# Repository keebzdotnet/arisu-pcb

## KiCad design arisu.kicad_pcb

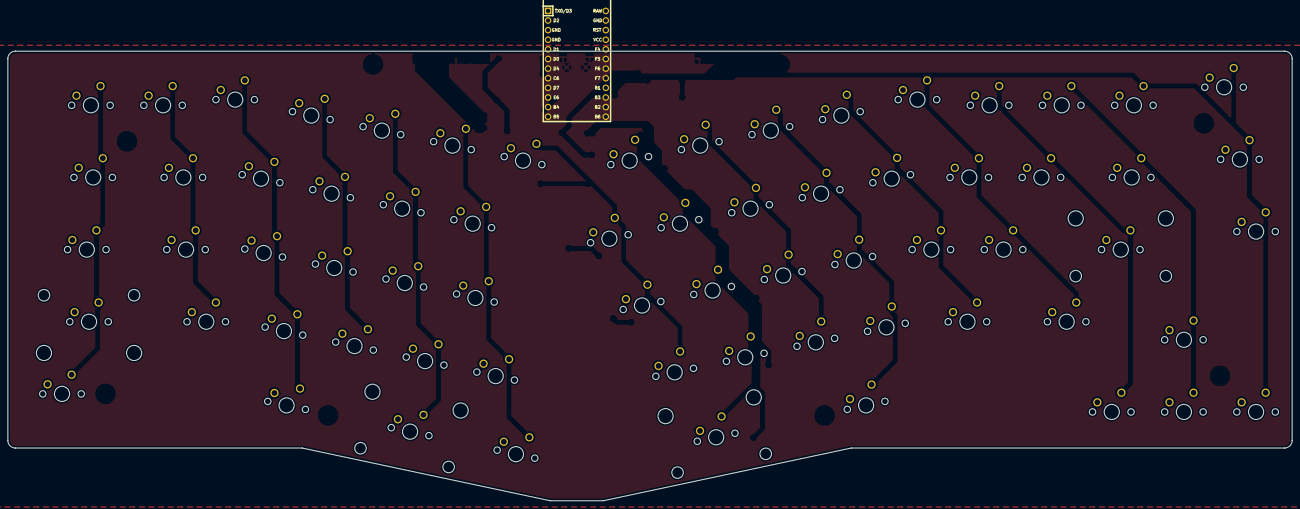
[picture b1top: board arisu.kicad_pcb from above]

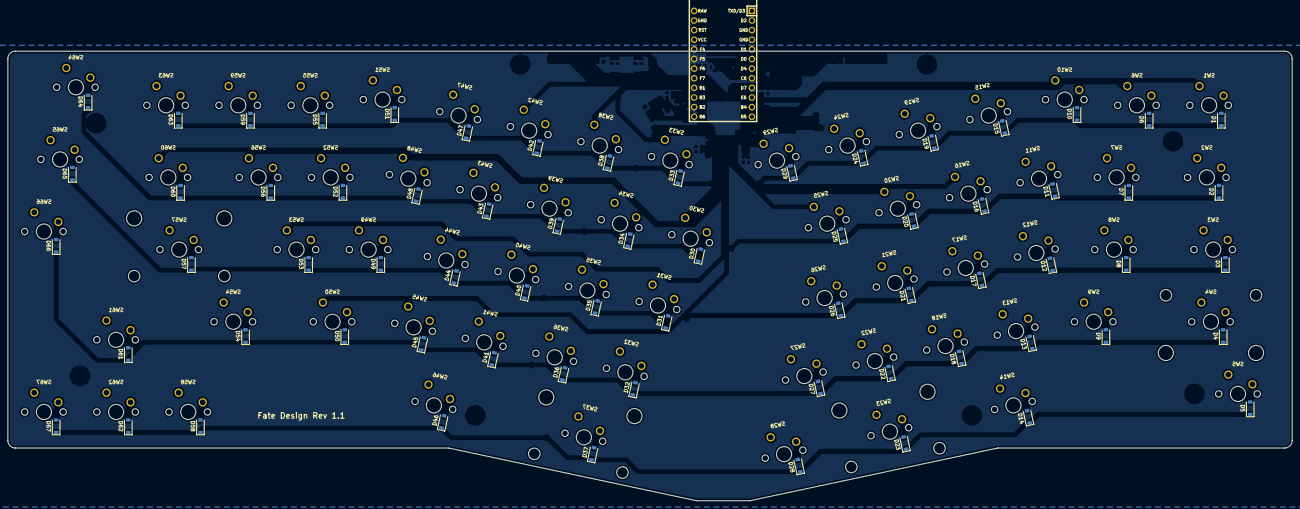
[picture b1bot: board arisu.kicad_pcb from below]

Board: 2 copper layers, 339.1 x 118.7 mm, 135 parts (67 on the bottom side), 82 nets, no tracks yet.

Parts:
D1, D2, D3, D4, D5, D6, D7, D8, D9, D10, D11, D12, D13, D14, D15, D16, D17, D18, D19, D20, D21, D22, D23, D24, D25, D26, D27, D28, D29, D30, D31, D32, D33, D34, D35, D36, D37, D38, D39, D40, D41, D42, D43, D44, D45, D46, D47, D48, D49, D50, D51, D52, D53, D54, D55, D56, D57, D58, D59, D60, D61, D62, D63, D64, D65, D66, D67: D; D_SOD-123
SW1, SW6, SW7, SW8, SW9, SW10, SW11, SW12, SW13, SW15, SW16, SW17, SW18, SW19, SW20, SW21, SW22, SW24, SW25, SW26, SW27, SW28, SW29, SW30, SW31, SW32, SW33, SW34, SW35, SW36, SW38, SW39, SW40, SW41, SW42, SW43, SW44, SW45, SW47, SW48, SW49, SW50, SW51, SW52, SW53, SW55, SW56, SW58, SW59, SW61, SW62, SW63, SW64, SW65, SW66, SW67: SW_Push; SW_Cherry_MX_1.00u_PCB
SW2, SW5, SW14, SW46, SW60: SW_Push; SW_Cherry_MX_1.50u_PCB
SW3, SW54: SW_Push; SW_Cherry_MX_1.75u_PCB
SW4: SW_Push; SW_Cherry_MX_2.25u_PCB
SW23: SW_Push; SW_Cherry_MX_2.00u_PCB_ReversedStabilizers
SW37: SW_Push; SW_Cherry_MX_2.75u_PCB_ReversedStabilizers
SW57: SW_Push; SW_Cherry_MX_2.25u_PCB_ReversedStabilizers
U1: ProMicro; ArduinoProMicro

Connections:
/matrix/col0: SW1.1, SW2.1, SW3.1, SW4.1, SW5.1, SW6.1, SW7.1, SW8.1, SW9.1, U1.12
/matrix/col2: SW10.1, SW11.1, SW12.1, SW13.1, SW14.1
/matrix/col3: SW15.1, SW16.1, SW17.1, SW18.1, U1.11
/matrix/col4: SW19.1, SW20.1, SW21.1, SW22.1, SW23.1, SW24.1, SW25.1, SW26.1, SW27.1, SW28.1, U1.10
/matrix/col6: SW29.1, SW30.1, SW31.1, SW32.1, SW33.1, SW34.1, SW35.1, SW36.1, SW37.1, U1.9
/matrix/col8: SW38.1, SW39.1, SW40.1, SW41.1, U1.8
/matrix/col9: SW42.1, SW43.1, SW44.1, SW45.1, SW46.1
/matrix/col10: SW47.1, SW48.1, SW49.1, SW50.1, SW51.1, SW52.1, SW53.1, SW54.1, U1.7
/matrix/col12: SW55.1, SW56.1, SW57.1, SW58.1, U1.6
/matrix/col13: SW59.1, SW60.1, SW61.1, SW62.1
/matrix/col14: SW63.1, SW64.1, SW65.1, SW66.1, SW67.1, U1.5
/matrix/row0: D1.1, D6.1, D10.1, D15.1, D19.1, D24.1, D29.1, D33.1, D38.1, D42.1, D47.1, D51.1, D55.1, D59.1, D63.1, U1.20
/matrix/row1: D2.1, D3.1, D7.1, D8.1, D11.1, D12.1, D16.1, D17.1, D20.1, D21.1, D25.1, D26.1, D30.1, D31.1, D34.1, D35.1, D39.1, D40.1, D43.1, D44.1, D48.1, D49.1, D52.1, D53.1, D56.1, D57.1, D60.1, D64.1, D65.1, U1.18, U1.19
/matrix/row3: D4.1, D9.1, D13.1, D18.1, D22.1, D27.1, D32.1, D36.1, D41.1, D45.1, D50.1, D54.1, D61.1, D66.1
/matrix/row4: D5.1, D14.1, D23.1, D28.1, D37.1, D46.1, D58.1, D62.1, D67.1, U1.16
unnamed: D1.2, SW1.2
unnamed: D2.2, SW2.2
unnamed: D3.2, SW3.2
unnamed: D4.2, SW4.2
unnamed: D5.2, SW5.2
unnamed: D6.2, SW6.2
unnamed: D7.2, SW7.2
unnamed: D8.2, SW8.2
unnamed: D9.2, SW9.2
unnamed: D10.2, SW10.2
unnamed: D11.2, SW11.2
unnamed: D12.2, SW12.2
unnamed: D13.2, SW13.2
unnamed: D14.2, SW14.2
unnamed: D15.2, SW15.2
unnamed: D16.2, SW16.2
unnamed: D17.2, SW17.2
unnamed: D18.2, SW18.2
unnamed: D19.2, SW19.2
unnamed: D20.2, SW20.2
unnamed: D21.2, SW21.2
unnamed: D22.2, SW22.2
unnamed: D23.2, SW23.2
unnamed: D24.2, SW24.2
unnamed: D25.2, SW25.2
unnamed: D26.2, SW26.2
unnamed: D27.2, SW27.2
unnamed: D28.2, SW28.2
unnamed: D29.2, SW29.2
unnamed: D30.2, SW30.2
unnamed: D31.2, SW31.2
unnamed: D32.2, SW32.2
unnamed: D33.2, SW33.2
unnamed: D34.2, SW34.2
unnamed: D35.2, SW35.2
unnamed: D36.2, SW36.2
unnamed: D37.2, SW37.2
unnamed: D38.2, SW38.2
unnamed: D39.2, SW39.2
unnamed: D40.2, SW40.2
unnamed: D41.2, SW41.2
unnamed: D42.2, SW42.2
unnamed: D43.2, SW43.2
unnamed: D44.2, SW44.2
unnamed: D45.2, SW45.2
unnamed: D46.2, SW46.2
unnamed: D47.2, SW47.2
unnamed: D48.2, SW48.2
unnamed: D49.2, SW49.2
unnamed: D50.2, SW50.2
unnamed: D51.2, SW51.2
unnamed: D52.2, SW52.2
unnamed: D53.2, SW53.2
unnamed: D54.2, SW54.2
unnamed: D55.2, SW55.2
unnamed: D56.2, SW56.2
unnamed: D57.2, SW57.2
unnamed: D58.2, SW58.2
unnamed: D59.2, SW59.2
unnamed: D60.2, SW60.2
unnamed: D61.2, SW61.2
unnamed: D62.2, SW62.2
unnamed: D63.2, SW63.2
unnamed: D64.2, SW64.2
unnamed: D65.2, SW65.2
unnamed: D66.2, SW66.2
unnamed: D67.2, SW67.2

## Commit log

2020-05-31 got rid of the MCU and added a pro micro
